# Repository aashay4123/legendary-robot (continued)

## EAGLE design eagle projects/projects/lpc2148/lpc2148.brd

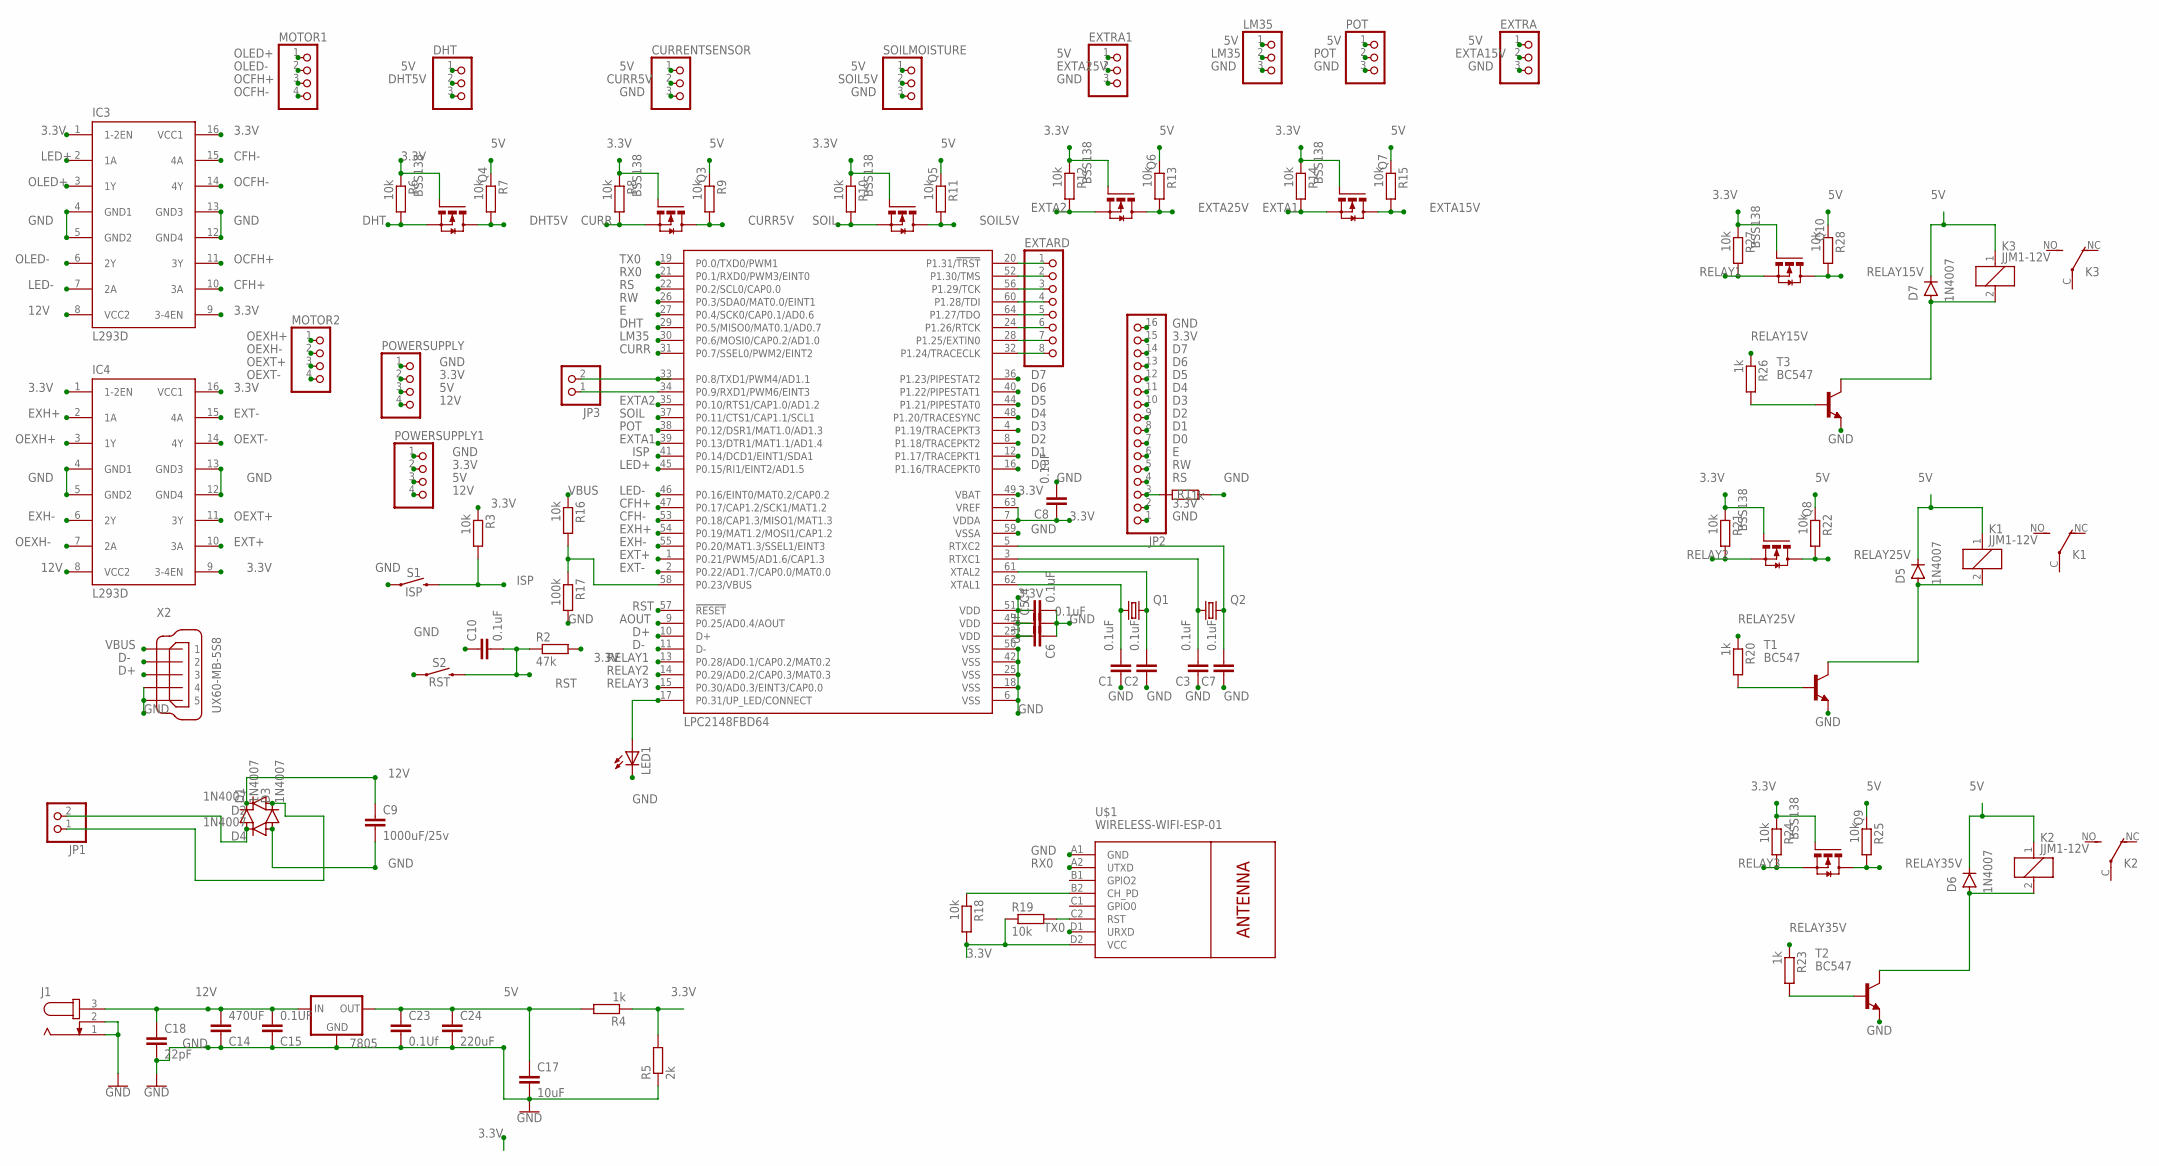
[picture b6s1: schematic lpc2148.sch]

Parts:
7805: 78XXL
C1, C2, C3, C4, C5, C6, C7, C8, C10: 0.1uF; 0603
C9: 1000uF/25v; 0603
C14: 470UF; 0603
C15: 0.1UF; 0603
C17: 10uF; 0603
C18: 22pF; 0603
C23: 0.1Uf; 0603
C24: 220uF; 0603
CURRENTSENSOR: PINHD-1X3; 1X03
D1, D2, D3, D4: 1N4007; DO41-10
D5, D6, D7: 1N4007; DO-41
DHT: PINHD-1X3; 1X03
EXTARD: PINHD-1X8-3.5MM; 1X08-3.5MM
EXTRA, EXTRA1: PINHD-1X3; 1X03
IC3, IC4: L293D; DIL16
J1: JACK-PLUG1; SPC4078
JP1, JP3: PINHD-1X2; 1X02
JP2: PINHD-1X16; 1X16
K1, K2, K3: JJM1-12V; JJM1C
LED1: LED5MM
LM35: PINHD-1X3; 1X03
MOTOR1, MOTOR2: PINHD-1X4; 1X04
POT: PINHD-1X3; 1X03
POWERSUPPLY, POWERSUPPLY1: PINHD-1X4; 1X04
Q1, Q2: KX-12B; 6.0X3.5_2
Q3, Q4, Q5, Q6, Q7, Q8, Q9, Q10: BSS138; SOT23-3
R1, R4, R20, R23, R26: 1k; 0204/5
R2: 47k; 0204/5
R3, R6, R7, R8, R9, R10, R11, R12, R13, R14, R15, R16, R18, R19, R21, R22, R24, R25, R27, R28: 10k; 0204/5
R5: 2k; 0204/5
R17: 100k; 0204/5
S1: ISP; TACTILE_SWITCH_PTH_6.0MM_KIT
S2: RST; TACTILE_SWITCH_PTH_6.0MM_KIT
SOILMOISTURE: PINHD-1X3; 1X03
T1, T2, T3: BC547; TO92
U1: LPC2148FBD64; TSQFP50P1200X1200X160-64N
U$1: WIRELESS-WIFI-ESP-01
X2: UX60-MB-5S8

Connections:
3.3V: C4.1, C5.1, C6.2, C8.1, IC3.1 (1-2EN), IC3.9 (3-4EN), IC3.16 (VCC1), IC4.1 (1-2EN), IC4.9 (3-4EN), IC4.16 (VCC1), JP2.2, JP2.15, POWERSUPPLY.2, POWERSUPPLY1.2, Q3.1 (G), Q4.1 (G), Q5.1 (G), Q6.1 (G), Q7.1 (G), Q8.1 (G), Q9.1 (G), Q10.1 (G), R2.2, R3.1, R4.1, R5.2, R6.1, R8.1, R10.1, R12.1, R14.1, R18.2, R19.1, R21.1, R24.1, R27.1, U1.7 (VDDA), U1.23 (VDD), U1.43 (VDD), U1.49 (VBAT), U1.51 (VDD), U1.63 (VREF), U$1.D2 (VCC)
5V: 7805.OUT, C17.1, C23.1, C24.1, CURRENTSENSOR.1, D5.C, D6.C, D7.C, DHT.1, EXTRA.1, EXTRA1.1, K1.1, K2.1, K3.1, LM35.1, POT.1, POWERSUPPLY.3, POWERSUPPLY1.3, R4.2, R7.1, R9.1, R11.1, R13.1, R15.1, R22.1, R25.1, R28.1, SOILMOISTURE.1
12V: 7805.IN, C9.1, C14.1, C15.1, C18.1, D1.C, D2.C, IC3.8 (VCC2), IC4.8 (VCC2), J1.3, POWERSUPPLY.4, POWERSUPPLY1.4
AOUT: U1.9 (P0.25/AD0.4/AOUT)
CFH+: IC3.10 (3A), U1.47 (P0.17/CAP1.2/SCK1/MAT1.2)
CFH-: IC3.15 (4A), U1.53 (P0.18/CAP1.3/MISO1/MAT1.3)
CURR: Q3.2 (S), R8.2, U1.31 (P0.7/SSEL0/PWM2/EINT2)
CURR5V: CURRENTSENSOR.2, Q3.3 (D), R9.2
D0: JP2.7, U1.16 (P1.16/TRACEPKT0)
D1: JP2.8, U1.12 (P1.17/TRACEPKT1)
D2: JP2.9, U1.8 (P1.18/TRACEPKT2)
D3: JP2.10, U1.4 (P1.19/TRACEPKT3)
D4: JP2.11, U1.48 (P1.20/TRACESYNC)
D5: JP2.12, U1.44 (P1.21/PIPESTAT0)
D6: JP2.13, U1.40 (P1.22/PIPESTAT1)
D7: JP2.14, U1.36 (P1.23/PIPESTAT2)
D+: U1.10 (D+), X2.3
D-: U1.11 (D-), X2.2
DHT: Q4.2 (S), R6.2, U1.29 (P0.5/MISO0/MAT0.1/AD0.7)
DHT5V: DHT.2, Q4.3 (D), R7.2
E: JP2.6, U1.27 (P0.4/SCK0/CAP0.1/AD0.6)
EXH+: IC4.2 (1A), U1.54 (P0.19/MAT1.2/MOSI1/CAP1.2)
EXH-: IC4.6 (2Y), U1.55 (P0.20/MAT1.3/SSEL1/EINT3)
EXT+: IC4.10 (3A), U1.1 (P0.21/PWM5/AD1.6/CAP1.3)
EXT-: IC4.15 (4A), U1.2 (P0.22/AD1.7/CAP0.0/MAT0.0)
EXTA1: Q7.2 (S), R14.2, U1.39 (P0.13/DTR1/MAT1.1/AD1.4)
EXTA2: Q6.2 (S), R12.2, U1.35 (P0.10/RTS1/CAP1.0/AD1.2)
EXTA15V: EXTRA.2, Q7.3 (D), R15.2
EXTA25V: EXTRA1.2, Q6.3 (D), R13.2
GND: 7805.GND, C1.1, C2.1, C3.1, C4.2, C5.2, C6.1, C7.1, C8.2, C9.2, C10.1, C14.2, C15.2, C17.2, C18.2, C23.2, C24.2, CURRENTSENSOR.3, D3.A, D4.A, DHT.3, EXTRA.3, EXTRA1.3, IC3.4 (GND1), IC3.5 (GND2), IC3.12 (GND4), IC3.13 (GND3), IC4.4 (GND1), IC4.5 (GND2), IC4.12 (GND4), IC4.13 (GND3), J1.1, J1.2, JP2.1, JP2.16, LED1.K (C), LM35.3, POT.3, POWERSUPPLY.1, POWERSUPPLY1.1, R1.1, R5.1, R17.2, S1.1, SOILMOISTURE.3, T1.1 (E), T2.1 (E), T3.1 (E), U1.6 (VSS), U1.18 (VSS), U1.25 (VSS), U1.42 (VSS), U1.50 (VSS), U1.59 (VSSA), U$1.A1 (GND), X2.4, X2.5
ISP: R3.2, S1.3 (2), U1.41 (P0.14/DCD1/EINT1/SDA1)
LED+: IC3.2 (1A), U1.45 (P0.15/RI1/EINT2/AD1.5)
LED-: IC3.7 (2A), U1.46 (P0.16/EINT0/MAT0.2/CAP0.2)
LM35: LM35.2, U1.30 (P0.6/MOSI0/CAP0.2/AD1.0)
unnamed: C1.2, Q1.1, U1.62 (XTAL1)
unnamed: C2.2, Q1.2, U1.61 (XTAL2)
unnamed: C3.2, Q2.1, U1.3 (RTXC1)
unnamed: C7.2, Q2.2, U1.5 (RTXC2)
unnamed: D1.A, D4.C, JP1.2
unnamed: D2.A, D3.C, JP1.1
unnamed: JP3.2, U1.33 (P0.8/TXD1/PWM4/AD1.1)
unnamed: JP3.1, U1.34 (P0.9/RXD1/PWM6/EINT3)
unnamed: D6.A, K2.2, T2.3 (C)
unnamed: LED1.A, U1.17 (P0.31/UP_LED/CONNECT)
unnamed: D5.A, K1.2, T1.3 (C)
unnamed: R20.2, T1.2 (B)
unnamed: EXTARD.1, U1.20 (P1.31/!TRST)
unnamed: EXTARD.2, U1.52 (P1.30/TMS)
unnamed: EXTARD.3, U1.56 (P1.29/TCK)
unnamed: R16.2, R17.1, U1.58 (P0.23/VBUS)
unnamed: EXTARD.4, U1.60 (P1.28/TDI)
unnamed: EXTARD.5, U1.64 (P1.27/TDO)
unnamed: JP2.3, R1.2
unnamed: R23.2, T2.2 (B)
unnamed: EXTARD.6, U1.24 (P1.26/RTCK)
unnamed: EXTARD.7, U1.28 (P1.25/EXTIN0)
unnamed: EXTARD.8, U1.32 (P1.24/TRACECLK)
unnamed: R18.1, U$1.B2 (CH_PD)
unnamed: R19.2, U$1.C2 (RST)
unnamed: D7.A, K3.2, T3.3 (C)
unnamed: R26.2, T3.2 (B)
OCFH+: IC3.11 (3Y), MOTOR1.3
OCFH-: IC3.14 (4Y), MOTOR1.4
OEXH+: IC4.3 (1Y), MOTOR2.1
OEXH-: IC4.7 (2A), MOTOR2.2
OEXT+: IC4.11 (3Y), MOTOR2.3
OEXT-: IC4.14 (4Y), MOTOR2.4
OLED+: IC3.3 (1Y), MOTOR1.1
OLED-: IC3.6 (2Y), MOTOR1.2
POT: POT.2, U1.38 (P0.12/DSR1/MAT1.0/AD1.3)
RELAY1: Q10.2 (S), R27.2, U1.13 (P0.28/AD0.1/CAP0.2/MAT0.2)
RELAY2: Q8.2 (S), R21.2, U1.14 (P0.29/AD0.2/CAP0.3/MAT0.3)
RELAY3: Q9.2 (S), R24.2, U1.15 (P0.30/AD0.3/EINT3/CAP0.0)
RELAY15V: Q10.3 (D), R26.1, R28.2
RELAY25V: Q8.3 (D), R20.1, R22.2
RELAY35V: Q9.3 (D), R23.1, R25.2
RS: JP2.4, U1.22 (P0.2/SCL0/CAP0.0)
RST: C10.2, R2.1, S2.3 (2), U1.57 (!RESET)
RW: JP2.5, U1.26 (P0.3/SDA0/MAT0.0/EINT1)
RX0: U1.21 (P0.1/RXD0/PWM3/EINT0), U$1.A2 (UTXD)
SOIL: Q5.2 (S), R10.2, U1.37 (P0.11/CTS1/CAP1.1/SCL1)
SOIL5V: Q5.3 (D), R11.2, SOILMOISTURE.2
TX0: U1.19 (P0.0/TXD0/PWM1), U$1.D1 (URXD)
VBUS: R16.1, X2.1

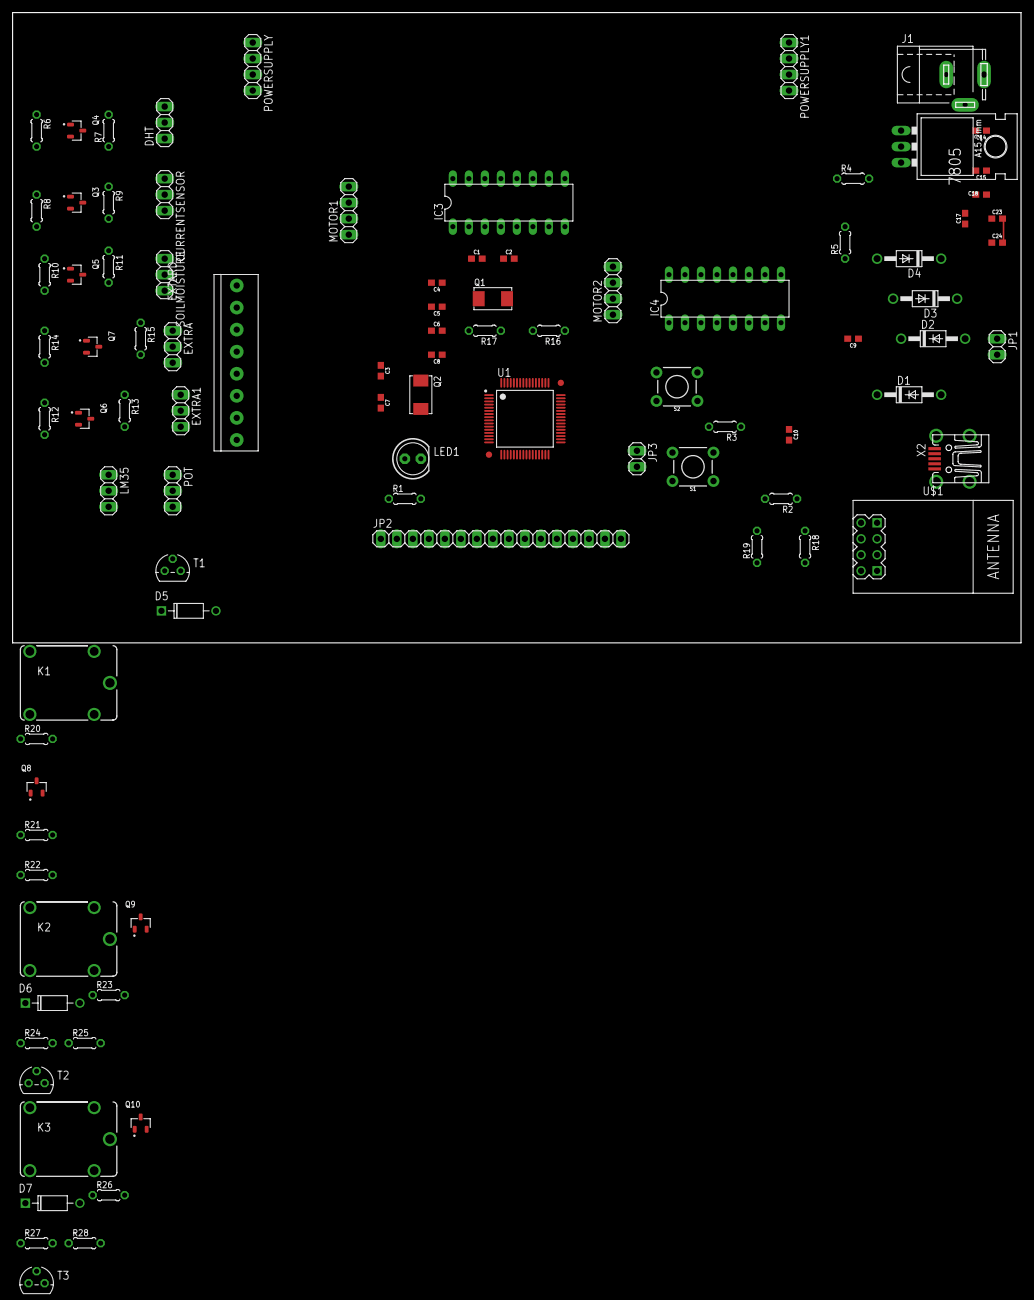
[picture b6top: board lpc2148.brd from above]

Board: 2 copper layers, 160.0 x 100.0 mm, 92 parts (0 on the bottom side), 83 nets.

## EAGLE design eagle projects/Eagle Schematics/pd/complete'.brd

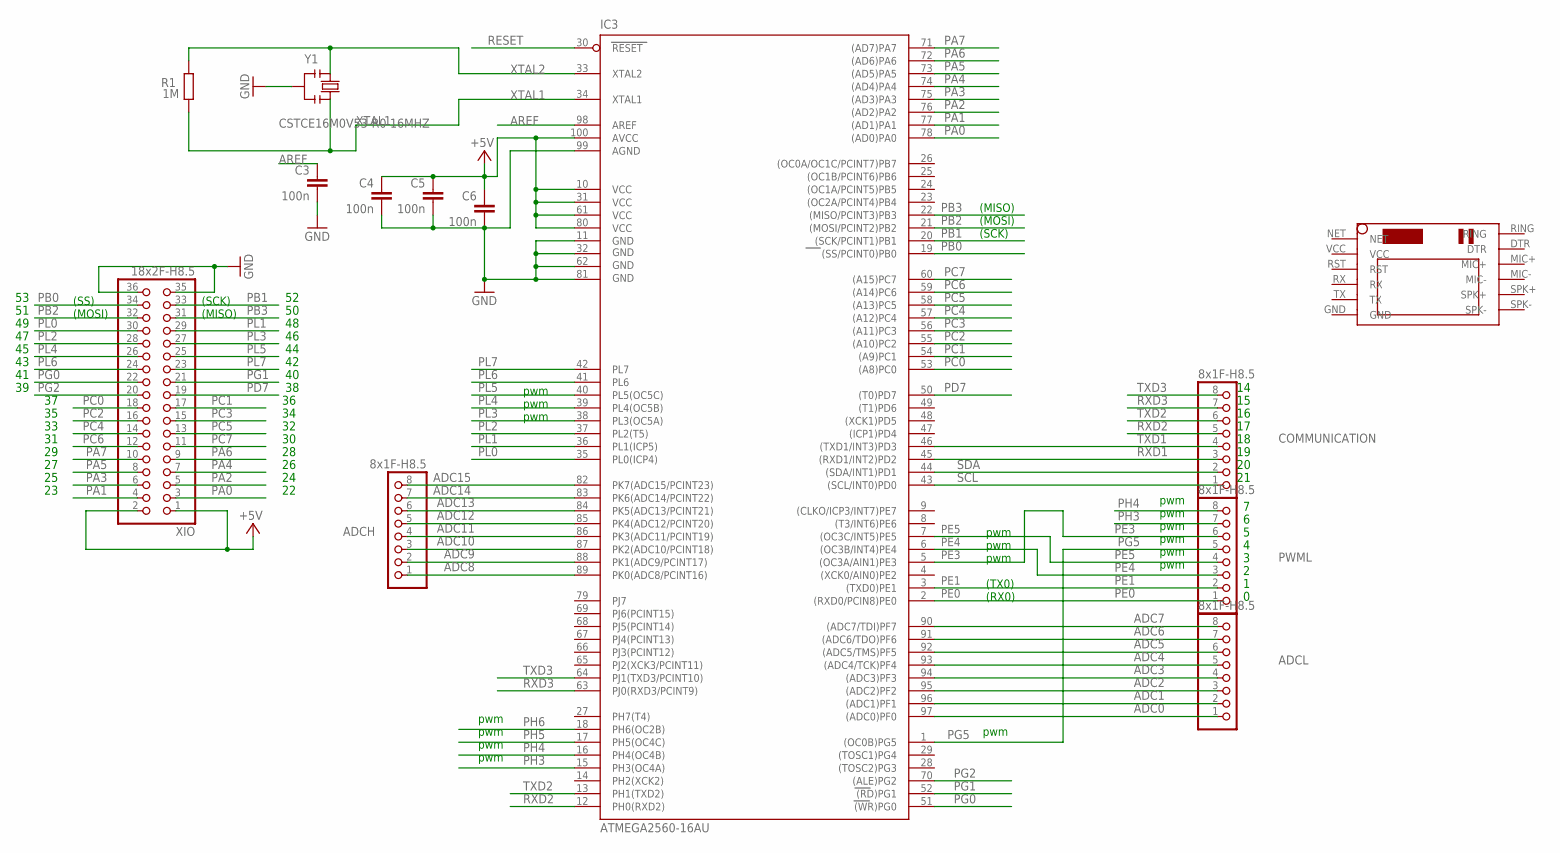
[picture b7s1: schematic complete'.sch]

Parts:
ADCH: 8x1F-H8.5; 1X08
ADCL: 8x1F-H8.5; 1X08
C3, C4, C5, C6: 100n; C0603-ROUND
COMMUNICATION: 8x1F-H8.5; 1X08
IC3: ATMEGA2560-16AU; TQFP100
PWML: 8x1F-H8.5; 1X08
R1: 1M; R0603-ROUND
U$1: SIM800LMODULE
XIO: 18x2F-H8.5; 2X18
Y1: CSTCE16M0V53-R0 16MHZ; RESONATOR

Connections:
+5V: C4.1, C5.1, C6.1, IC3.10 (VCC), IC3.31 (VCC1), IC3.61 (VCC2), IC3.80 (VCC3), IC3.100 (AVCC), XIO.1, XIO.2
ADC0: ADCL.1, IC3.97 ((ADC0)PF0)
ADC1: ADCL.2, IC3.96 ((ADC1)PF1)
ADC2: ADCL.3, IC3.95 ((ADC2)PF2)
ADC3: ADCL.4, IC3.94 ((ADC3)PF3)
ADC4: ADCL.5, IC3.93 ((ADC4/TCK)PF4)
ADC5: ADCL.6, IC3.92 ((ADC5/TMS)PF5)
ADC6: ADCL.7, IC3.91 ((ADC6/TDO)PF6)
ADC7: ADCL.8, IC3.90 ((ADC7/TDI)PF7)
ADC8: ADCH.1, IC3.89 (PK0(ADC8/PCINT16))
ADC9: ADCH.2, IC3.88 (PK1(ADC9/PCINT17))
ADC10: ADCH.3, IC3.87 (PK2(ADC10/PCINT18))
ADC11: ADCH.4, IC3.86 (PK3(ADC11/PCINT19))
ADC12: ADCH.5, IC3.85 (PK4(ADC12/PCINT20))
ADC13: ADCH.6, IC3.84 (PK5(ADC13/PCINT21))
ADC14: ADCH.7, IC3.83 (PK6(ADC14/PCINT22))
ADC15: ADCH.8, IC3.82 (PK7(ADC15/PCINT23))
AREF: C3.1, IC3.98 (AREF)
GND: C3.2, C4.2, C5.2, C6.2, IC3.11 (GND), IC3.32 (GND1), IC3.62 (GND2), IC3.81 (GND3), IC3.99 (AGND), XIO.35, XIO.36, Y1.2
PA0: IC3.78 ((AD0)PA0), XIO.3
PA1: IC3.77 ((AD1)PA1), XIO.4
PA2: IC3.76 ((AD2)PA2), XIO.5
PA3: IC3.75 ((AD3)PA3), XIO.6
PA4: IC3.74 ((AD4)PA4), XIO.7
PA5: IC3.73 ((AD5)PA5), XIO.8
PA6: IC3.72 ((AD6)PA6), XIO.9
PA7: IC3.71 ((AD7)PA7), XIO.10
PB0: IC3.19 ((SS/PCINT0)PB0), XIO.34
PB1: IC3.20 ((SCK/PCINT1)PB1), XIO.33
PB2: IC3.21 ((MOSI/PCINT2)PB2), XIO.32
PB3: IC3.22 ((MISO/PCINT3)PB3), XIO.31
PC0: IC3.53 ((A8)PC0), XIO.18
PC1: IC3.54 ((A9)PC1), XIO.17
PC2: IC3.55 ((A10)PC2), XIO.16
PC3: IC3.56 ((A11)PC3), XIO.15
PC4: IC3.57 ((A12)PC4), XIO.14
PC5: IC3.58 ((A13)PC5), XIO.13
PC6: IC3.59 ((A14)PC6), XIO.12
PC7: IC3.60 ((A15)PC7), XIO.11
PD7: IC3.50 ((T0)PD7), XIO.19
PE0: IC3.2 ((RXD0/PCIN8)PE0), PWML.1
PE1: IC3.3 ((TXD0)PE1), PWML.2
PE3: IC3.5 ((OC3A/AIN1)PE3), PWML.6
PE4: IC3.6 ((OC3B/INT4)PE4), PWML.3
PE5: IC3.7 ((OC3C/INT5)PE5), PWML.4
PG0: IC3.51 ((WR)PG0), XIO.22
PG1: IC3.52 ((RD)PG1), XIO.21
PG2: IC3.70 ((ALE)PG2), XIO.20
PG5: IC3.1 ((OC0B)PG5), PWML.5
PH3: IC3.15 (PH3(OC4A)), PWML.7
PH4: IC3.16 (PH4(OC4B)), PWML.8
PH5: IC3.17 (PH5(OC4C))
PH6: IC3.18 (PH6(OC2B))
PL0: IC3.35 (PL0(ICP4)), XIO.30
PL1: IC3.36 (PL1(ICP5)), XIO.29
PL2: IC3.37 (PL2(T5)), XIO.28
PL3: IC3.38 (PL3(OC5A)), XIO.27
PL4: IC3.39 (PL4(OC5B)), XIO.26
PL5: IC3.40 (PL5(OC5C)), XIO.25
PL6: IC3.41 (PL6), XIO.24
PL7: IC3.42 (PL7), XIO.23
RESET: IC3.30 (RESET)
RXD1: COMMUNICATION.3, IC3.45 ((RXD1/INT2)PD2)
RXD2: COMMUNICATION.5, IC3.12 (PH0(RXD2))
RXD3: COMMUNICATION.7, IC3.63 (PJ0(RXD3/PCINT9))
SCL: COMMUNICATION.1, IC3.43 ((SCL/INT0)PD0)
SDA: COMMUNICATION.2, IC3.44 ((SDA/INT1)PD1)
TXD1: COMMUNICATION.4, IC3.46 ((TXD1/INT3)PD3)
TXD2: COMMUNICATION.6, IC3.13 (PH1(TXD2))
TXD3: COMMUNICATION.8, IC3.64 (PJ1(TXD3/PCINT10))
XTAL1: IC3.34 (XTAL1), R1.1, Y1.3
XTAL2: IC3.33 (XTAL2), R1.2, Y1.1

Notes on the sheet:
pwm
(TX0)
(RX0)
(MISO)
(SCK)
(MOSI)
(SS)

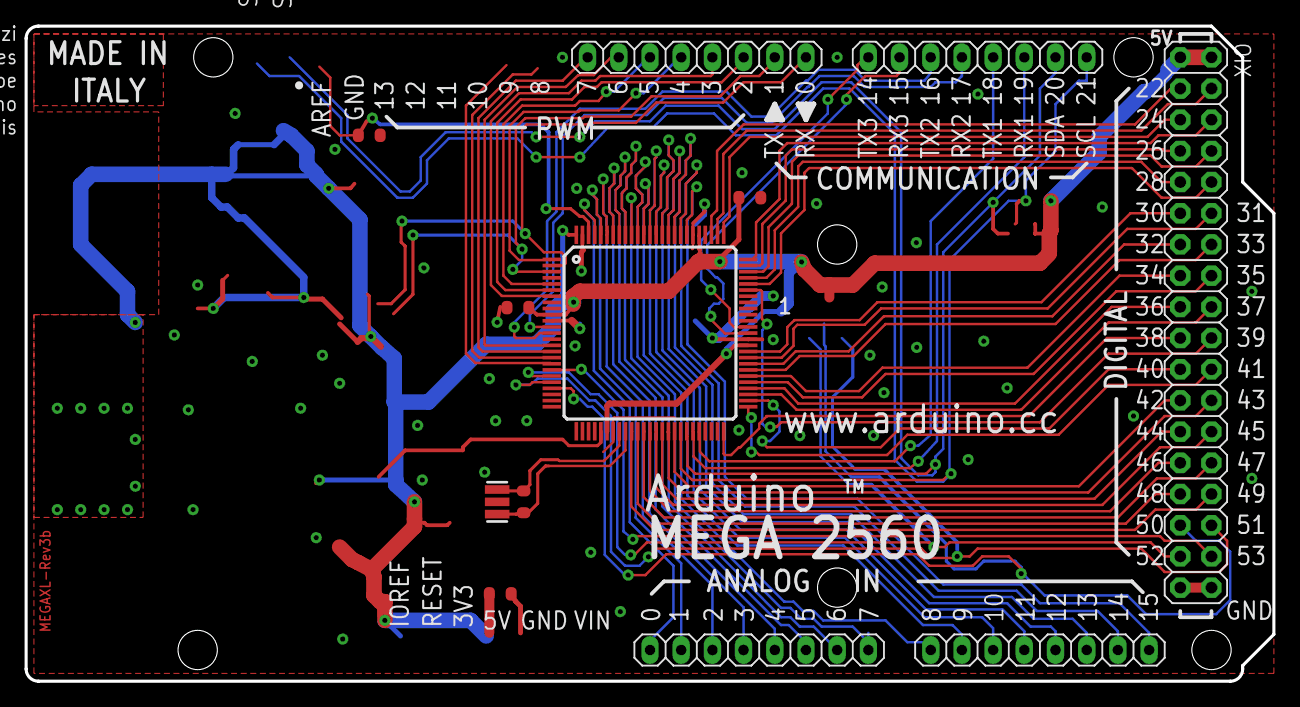
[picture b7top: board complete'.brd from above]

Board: 2 copper layers, 101.6 x 53.3 mm, 12 parts (0 on the bottom side), 69 nets.

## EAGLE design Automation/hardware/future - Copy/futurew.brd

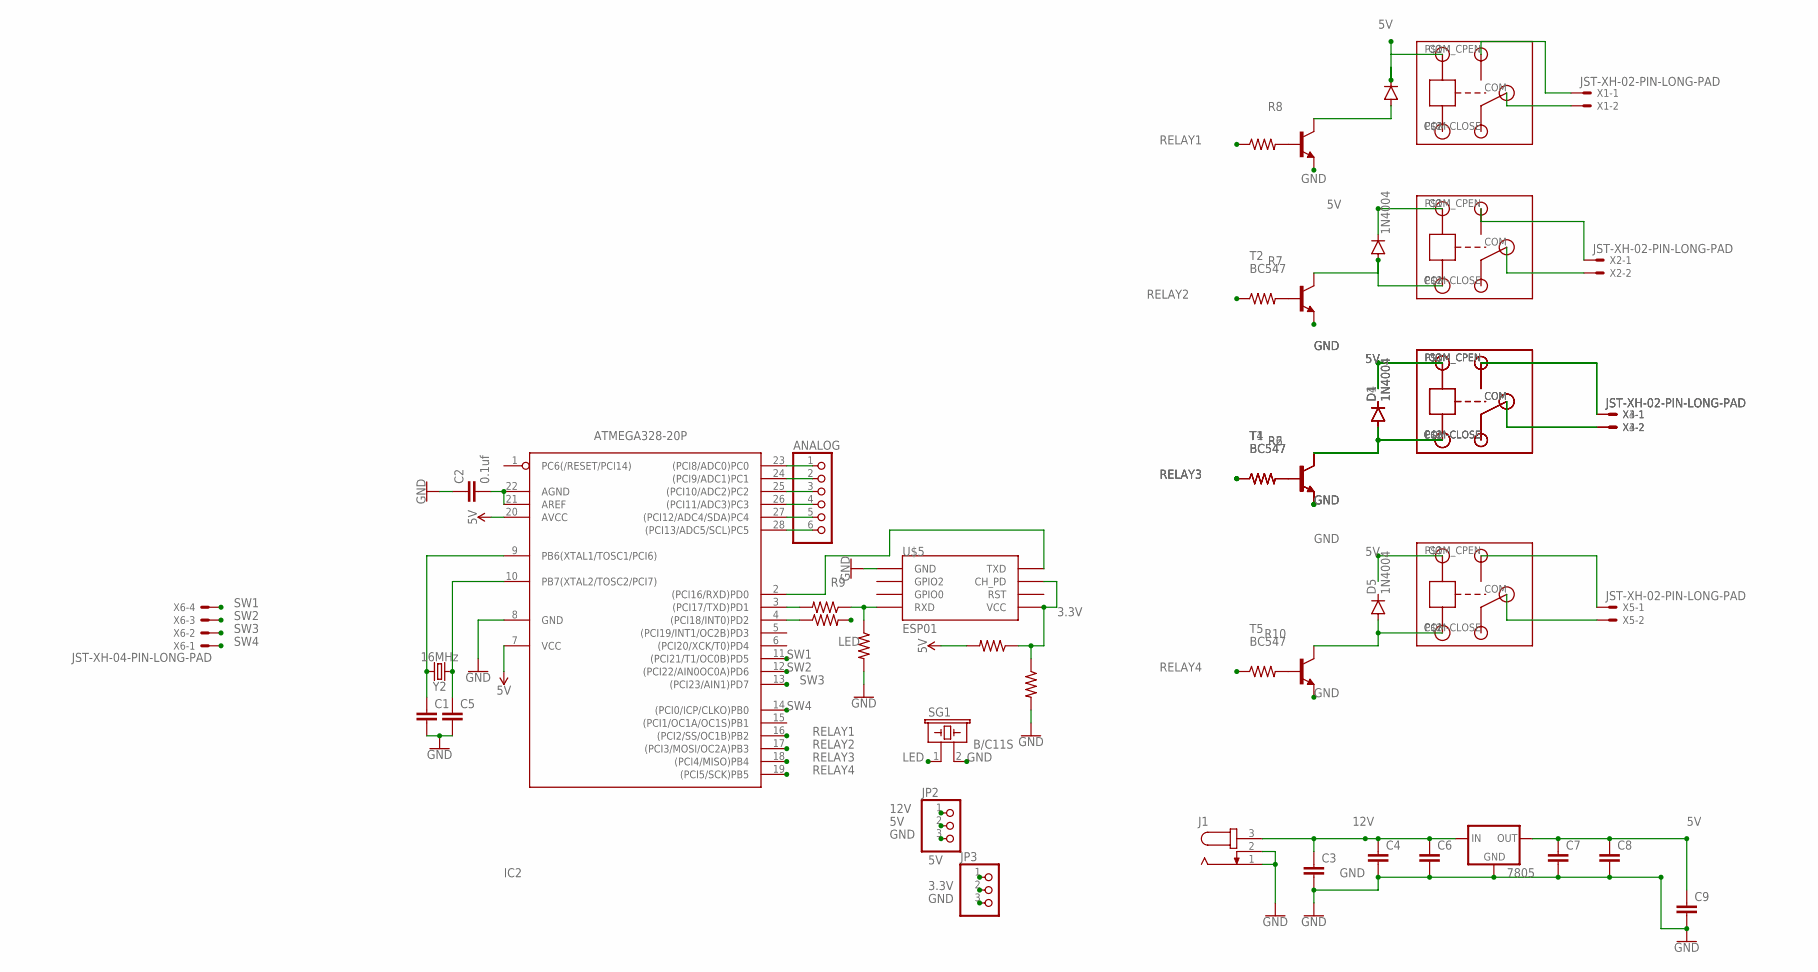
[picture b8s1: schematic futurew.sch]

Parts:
7805: 78XXL
ANALOG: PINHD-1X6; 1X06
C1, C3, C4, C5, C6, C7, C8, C9: C2,5-3; C2.5-3
C2: 0.1uf; C2.5-3
D1, D2, D3, D4, D5: 1N4004; DO41-10
IC2: ATMEGA328-20P; DIL28-3
J1: JACK-PLUG1; SPC4078
JP2, JP3: PINHD-1X3; 1X03
R1, R2, R4, R7, R8, R9, R10: 1k; AXIAL-0.3
R3, R5: 2k; AXIAL-0.3
R6: 10M; AXIAL-0.3
SG1: B/C11S
T1, T2, T3, T4, T5: BC547; TO92
U$1, U$2, U$3, U$4, U$6: RELAY
U$5: ESP01
X1, X2, X3, X4, X5: JST-XH-02-PIN-LONG-PAD; JST-XH-02-PACKAGE-LONG-PAD
X6: JST-XH-04-PIN-LONG-PAD; JST-XH-04-PACKAGE-LONG-PAD
Y2: 16MHz; HC49US

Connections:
3.3V: JP3.2, R4.P$1 (1), R5.P$1 (1), U$5.CH_PD, U$5.VCC
5V: 7805.OUT, C7.1, C8.1, C9.1, D2.C, D3.C, IC2.7 (VCC), IC2.20 (AVCC), JP2.2, JP3.1, R4.P$2 (2), U$1.P$1 (IN), U$2.P$1 (IN), U$3.P$1 (IN), U$4.P$1 (IN), U$6.P$1 (IN)
12V: 7805.IN, C3.1, C4.1, C6.1, J1.3, JP2.1
GND: 7805.GND, C1.2, C2.1, C3.2, C4.2, C5.2, C6.2, C7.2, C8.2, C9.2, IC2.8 (GND), J1.1, J1.2, JP2.3, JP3.3, R3.P$2 (2), R5.P$2 (2), SG1.2, T1.1 (E), T2.1 (E), T3.1 (E), T4.1 (E), T5.1 (E), U$5.GND
LED: R9.P$2 (2), SG1.1
unnamed: R1.P$1 (1), R3.P$1 (1), U$5.RX (RXD)
unnamed: IC2.3 ((PCI17/TXD)PD1), R1.P$2 (2)
unnamed: IC2.2 ((PCI16/RXD)PD0), U$5.TX (TXD)
unnamed: ANALOG.1, IC2.23 ((PCI8/ADC0)PC0)
unnamed: ANALOG.2, IC2.24 ((PCI9/ADC1)PC1)
unnamed: ANALOG.3, IC2.25 ((PCI10/ADC2)PC2)
unnamed: C2.2, IC2.21 (AREF), IC2.22 (AGND)
unnamed: ANALOG.4, IC2.26 ((PCI11/ADC3)PC3)
unnamed: ANALOG.5, IC2.27 ((PCI12/ADC4/SDA)PC4)
unnamed: ANALOG.6, IC2.28 ((PCI13/ADC5/SCL)PC5)
unnamed: D1.A, T1.3 (C), U$1.P$2 (GND)
unnamed: U$3.COM_CPEN (COM-OPEN), X1.1
unnamed: D2.A, T2.3 (C), U$2.P$2 (GND)
unnamed: D3.A, T3.3 (C)
unnamed: U$3.COM, X1.2
unnamed: U$2.COM, X2.2
unnamed: R6.P$2 (2), T1.2 (B)
unnamed: R7.P$2 (2), T2.2 (B)
unnamed: R8.P$2 (2), T3.2 (B)
unnamed: IC2.4 ((PCI18/INT0)PD2), R9.P$1 (1)
unnamed: U$2.COM_CPEN (COM-OPEN), X2.1
unnamed: U$1.COM, X3.2
unnamed: U$1.COM_CPEN (COM-OPEN), X3.1
unnamed: D4.A, T4.3 (C), U$4.P$2 (GND)
unnamed: R2.P$2 (2), T4.2 (B)
unnamed: U$4.COM, X4.2
unnamed: U$4.COM_CPEN (COM-OPEN), X4.1
unnamed: U$1.COM-CLOSE, U$4.COM-CLOSE
unnamed: D1.C, D4.C
unnamed: D5.A, T5.3 (C), U$6.P$2 (GND)
unnamed: R10.P$2 (2), T5.2 (B)
unnamed: U$6.COM, X5.2
unnamed: U$6.COM_CPEN (COM-OPEN), X5.1
unnamed: C5.1, IC2.10 (PB7(XTAL2/TOSC2/PCI7)), Y2.1
unnamed: C1.1, IC2.9 (PB6(XTAL1/TOSC1/PCI6)), Y2.2
RELAY1: IC2.16 ((PCI2/SS/OC1B)PB2), R8.P$1 (1)
RELAY2: IC2.17 ((PCI3/MOSI/OC2A)PB3), R7.P$1 (1)
RELAY3: IC2.18 ((PCI4/MISO)PB4), R2.P$1 (1), R6.P$1 (1)
RELAY4: IC2.19 ((PCI5/SCK)PB5), R10.P$1 (1)
SW1: IC2.11 ((PCI21/T1/OC0B)PD5), X6.4
SW2: IC2.12 ((PCI22/AIN0OC0A)PD6), X6.3
SW3: IC2.13 ((PCI23/AIN1)PD7), X6.2
SW4: IC2.14 ((PCI0/ICP/CLKO)PB0), X6.1

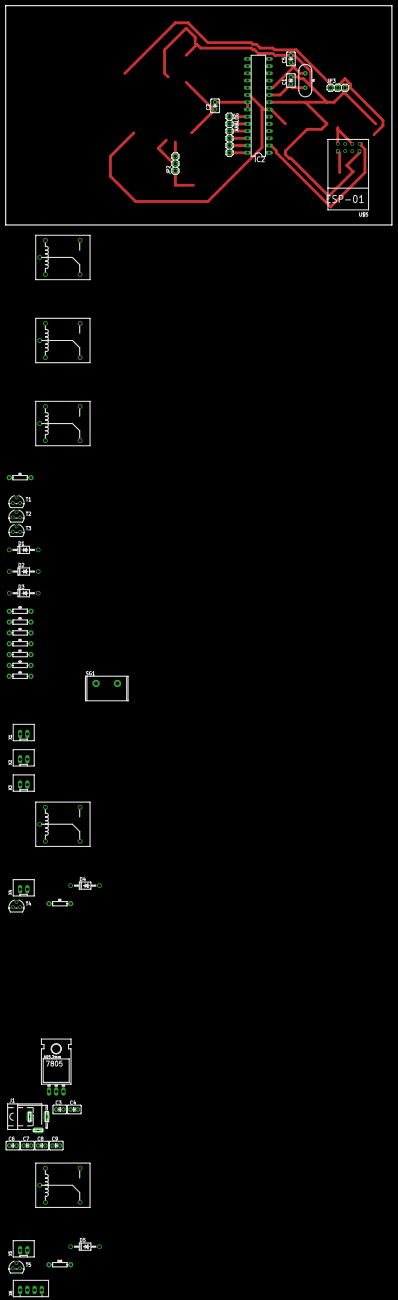
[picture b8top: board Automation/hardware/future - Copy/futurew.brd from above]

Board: 2 copper layers, 49 parts (0 on the bottom side), 48 nets.

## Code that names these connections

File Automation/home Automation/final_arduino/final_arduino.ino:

const int light1 = A5;
const int light2 = A4;
const int fan1 = A3;
const int fan2 = A2;
int i = 0;
int l1 = 2, l2 = 2, f1 = 2, f2 = 2;
const int relay1 = 9, relay2 = 10, relay3 = 11, relay4 = 12;
int f11 = 0, f20 = 0, l10 = 0, l20 = 0;
int f10 = 0, f21 = 0, l11 = 0, l21 = 0;
int fan1_cs = 2 , fan1_ss = 2, fan2_cs = 2, fan2_ss = 2;
int light1_cs = 2, light2_cs = 2 , light1_ss = 2 , light2_ss = 2;
String str, receivedData;
String value[5], post_wifi;
char msg1[20], combinedData[20];
long lastMsg = 0; // an array to store the received data
boolean newData = false;

void setup() {
  pinMode(relay1, OUTPUT);
  pinMode(relay2, OUTPUT);
  pinMode(relay3, OUTPUT);
  pinMode(relay4, OUTPUT);
  Serial.begin(115200);
}

void upload(char msg[20]) {
  char* token = strtok(msg, "/");
  int i = 0;
  while (token != NULL) {
    value[i] = token;
    token = strtok(NULL, "/");
    i++;
    if (value[0] == "home") {
      if (value[1] == "Lgt_1") {
        if (value[2] == "onn") {
          digitalWrite(relay1, HIGH);
     //     Serial.print("atm1/Lgt_1/onn/");
        } else if (value[2] == "off") {
          digitalWrite(relay1, LOW);
     //     Serial.print("atm1/Lgt_1/off/");
        }
      } else if (value[1] == "Lgt_2") {
        if (value[2] == "onn") {
          digitalWrite(relay2, HIGH);
    //      Serial.print("atm1/Lgt_2/onn/");
        } else if (value[2] == "off") {
          digitalWrite(relay2, LOW);
      //     Serial.print("atm1/Lgt_2/off/");
        }
      } else if (value[1] == "fan_1") {
        if (value[2] == "onn") {
     //      Serial.print("atm1/fan_1/onn/");
          digitalWrite(relay3, HIGH);
        } else if (value[2] == "off") {
      //     Serial.print("atm1/fan_1/off/");
          digitalWrite(relay3, LOW);
        }
      } else if (value[1] == "fan_2") {
        if (value[2] == "onn") {
          digitalWrite(relay4, HIGH);
        //  Serial.print("atm1/fan_2/onn/");
        } else if (value[2] == "off") {
          digitalWrite(relay4, LOW);
         // Serial.print("atm1/fan_2/off/");
        }
      }
    }
  }
}
void buttonState() {

  if (l11 > l10) {
    if (l1 == 1) {
      digitalWrite(relay1, HIGH);
      Serial.print("atm/Lgt_1/onn/");
      l11 = 0;
      l10 = 0;
      l1 = 2;
    }
  } else if (l11 < l10) {
    if (l1 == 2) {
      digitalWrite(relay1, LOW);
      Serial.print("atm/Lgt_1/off/");
      l11 = 0;
      l10 = 0;
      l1 = 1;
    }
  }
  if (l21 > l20) {
    if (l2 == 1) {
      digitalWrite(relay2, HIGH);
      Serial.print("atm/Lgt_2/onn/");
      l21 = 0;
      l20 = 0;
      l2 = 2;
    }
  } else if (l21 < l20) {
    if (l2 == 2) {
      digitalWrite(relay2, LOW);
      Serial.print("atm/Lgt_2/off/");
      l21 = 0;
      l20 = 0;
      l2 = 1;
    }
  }
  if (f11 > f10) {
    if (f1 == 1) {
      digitalWrite(relay3, HIGH);
      Serial.print("atm/fan_1/onn/");
      f11 = 0;
      f10 = 0;
      f1 = 2;
    }
  } else if (f11 < f10) {
    if (f1 == 2) {
      digitalWrite(relay3, LOW);
      Serial.print("atm/fan_1/off/");
      f11 = 0;
      f10 = 0;
      f1 = 1;
    }
  }
  if (f21 > f20) {
    if (f2 == 1) {
      digitalWrite(relay4, HIGH);
      Serial.print("atm/fan_2/onn/");
      f21 = 0;
      f20 = 0;
      f2 = 2;
    }
  } else if (f21 < f20) {
    if (f1 == 2) {
      digitalWrite(relay4, LOW);
      Serial.print("atm/fan_2/off/");
      f21 = 0;
      f20 = 0;
      f1 = 1;
    }
  }

}
void  buttoncheck() {
  if (light1_ss == 0) {
    l10 = l10 + 1;
  } else if (light1_ss == 1) {
    l11 = l11 + 1;
  }
  if (light2_ss == 0) {
    l20 = l20 + 1;
  } else if (light2_ss == 1) {
    l21 = l21 + 1;
  }
  if (fan1_ss == 0) {
    f10 = f10 + 1;
  } else if (fan1_ss == 1) {
    f11 = f11 + 1;
  }
  if (fan2_ss == 0) {
    f20 = f20 + 1;
  } else if (fan2_ss == 1) {
    f21 = f21 + 1;
  }
}
void loop() {
  while (i != 600) {
    light1_ss = analogRead(light1);
    light1_ss = light1_ss / 1023;
    delay(1);
    light2_ss = analogRead(light2);
    light2_ss = light2_ss / 1023;
    delay(1);
    fan1_ss = analogRead(fan1);
    fan1_ss = fan1_ss / 1023;
    delay(1);
    fan2_ss = analogRead(fan2);
    delay(1);
    fan2_ss = fan2_ss / 1023;
    buttoncheck();
    delay(1);
    i = i + 1;
  }
  buttonState();
  while (Serial.available()) {
    receivedData = Serial.readString();
    receivedData.toCharArray(combinedData, 20);
    upload(combinedData);
  }
  receivedData = "";
  i = 0;
}

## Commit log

2022-12-09 merged hardware repos
